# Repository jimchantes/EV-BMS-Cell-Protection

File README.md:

# EV Li-Ion Battery Cell Protection Circuit (Window Comparator)

An overvoltage and undervoltage monitoring circuit (BMS/AMS aspect) designed for a Formula Student Electric Vehicle (EV). The circuit monitors a single lithium-ion cell, ensuring it stays within the safe operating window of **3.0V to 4.2V**. If the cell voltage violates these parameters, the system triggers a **0V Fault Signal** to open the safety shutdowns.

## Project Structure
* `/Simulation`: LTspice circuit schematic and transient/DC sweep simulation files.
* `/Hardware`: KiCad schematic blueprints, footprint assignments, and PCB layout routing.

## Technical Specifications
* **Overvoltage Threshold (OV):** 4.2V
* **Undervoltage Threshold (UV):** 3.0V
* **Logic Output:** 5V (Safe Condition) / 0V (Fault Condition)
* **Threshold Reference:** Precision resistive ladder divider network (1.6kΩ / 2.4kΩ / 6.0kΩ) connected to a regulated 5V VCC line.

## Simulation & Validation (LTspice)
The circuit behavior was validated using LTspice. To bypass idealized push-pull macro-model contention, the window comparator output was isolated utilizing a diode network pulled up to a stable 5V rail.

*Result:* The simulation confirms a sharp, deterministic transition to 0V whenever the swept input voltage falls below 3.0V or exceeds 4.2V.

## Hardware Design (KiCad PCB)
The validated schematic was fully routed into a functional, single-layer Through-Hole (THT) PCB optimized for easy benchtop prototyping and verification.

* **Core IC:** LM393 Dual Differential Comparator (DIP-8 package)
* **Routing:** 45-degree trace angles to minimize EMI and maintain professional manufacturing standards.
* **Connector:** 4-Pin terminal header separating Vin (Cell Monitor), VCC (5V System Power), GND, and the Fault Output.

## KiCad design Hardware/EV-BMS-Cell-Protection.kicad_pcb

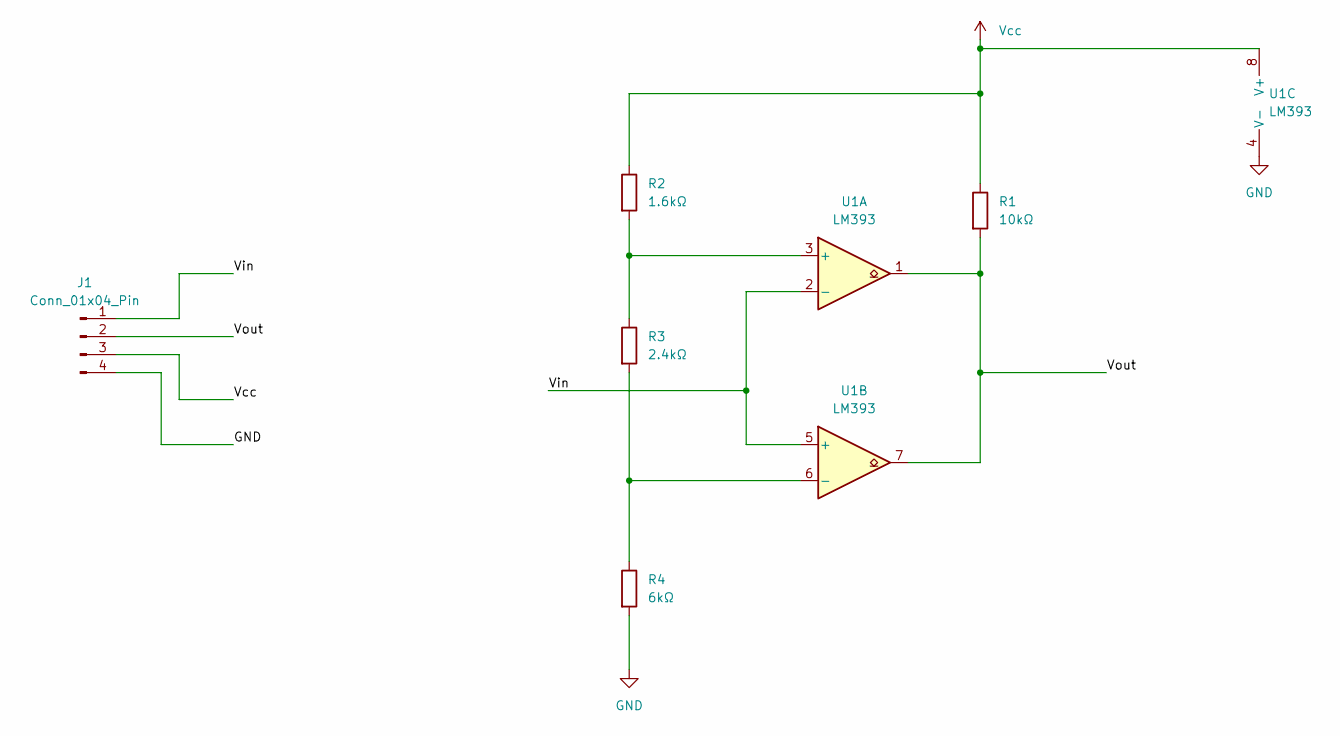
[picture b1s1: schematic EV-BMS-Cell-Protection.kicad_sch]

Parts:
J1: Conn_01x04_Pin; PinSocket_1x04_P2.54mm_Vertical
R1: 10kΩ; R_0805_2012Metric
R2: 1.6kΩ; R_0805_2012Metric
R3: 2.4kΩ; R_0805_2012Metric
R4: 6kΩ; R_0805_2012Metric
U1: LM393; DIP-8_W7.62mm

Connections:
/Vin: J1.1, U1.2 (-), U1.5 (+)
/Vout: J1.2, R1.2, U1.1, U1.7
GND: J1.4, R4.2, U1.4 (V-)
unnamed: R2.2, R3.1, U1.3 (+)
unnamed: R3.2, R4.1, U1.6 (-)
Vcc: J1.3, R1.1, R2.1, U1.8 (V+)

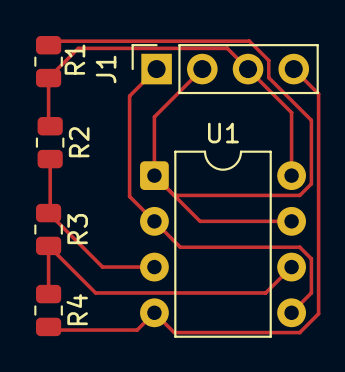
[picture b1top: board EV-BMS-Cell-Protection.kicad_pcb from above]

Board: 2 copper layers, 6 parts (0 on the bottom side), 6 nets.
